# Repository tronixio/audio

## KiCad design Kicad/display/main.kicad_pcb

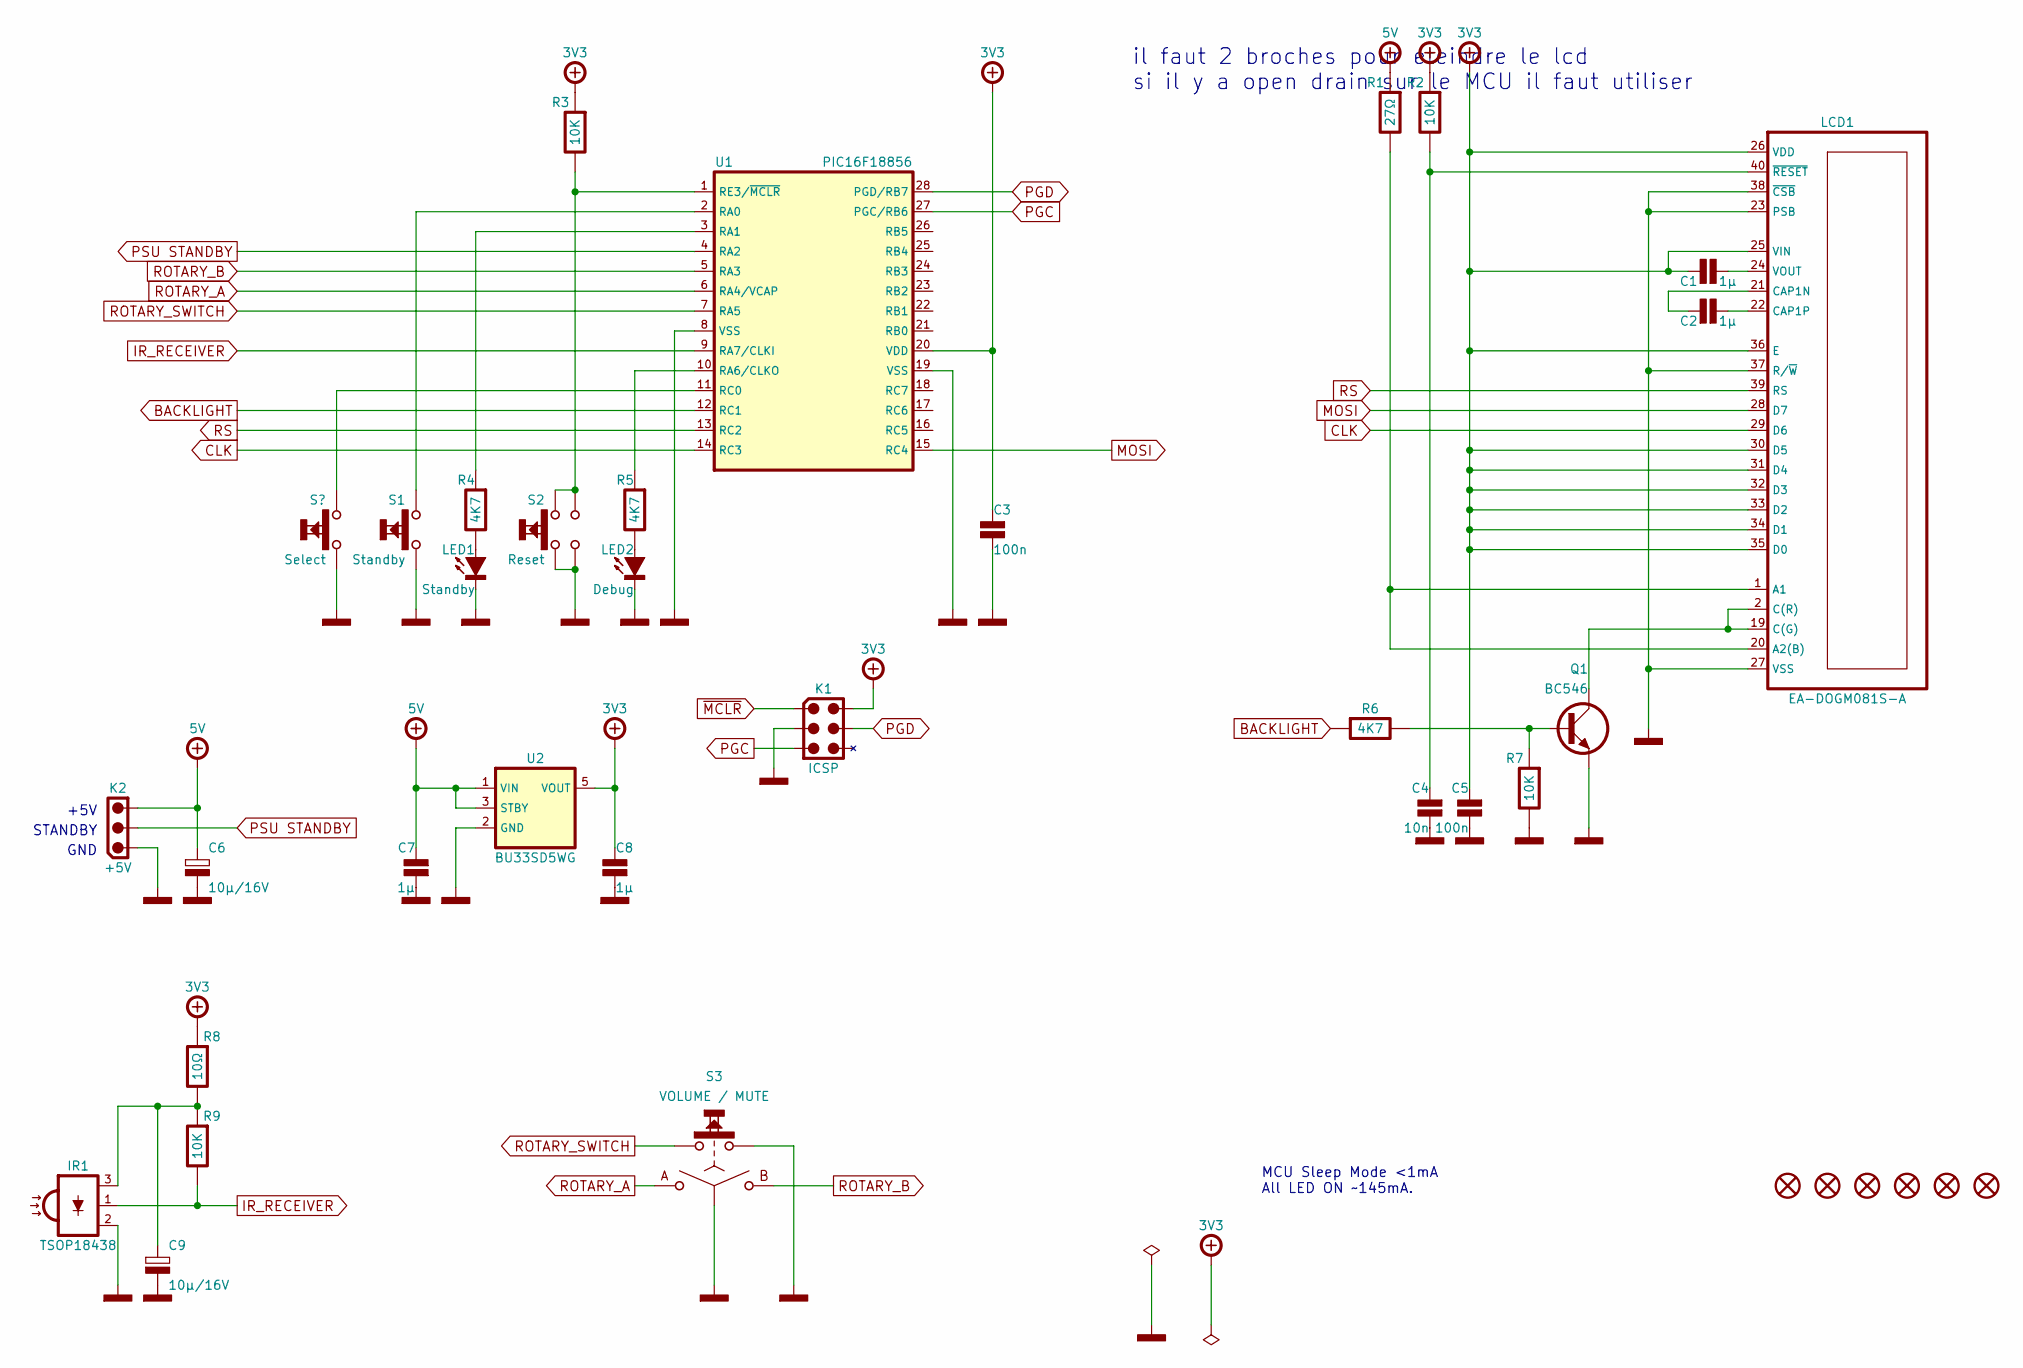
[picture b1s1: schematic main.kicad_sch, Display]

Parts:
C1, C2, C7, C8: 1µ; CAPACITOR-SMD-1206; Voltage 50V; Tolerance 20%; Mouser 80-C1206C105M5R
C3, C5: 100n; CAPACITOR-SMD-1206; Voltage 50V; Tolerance 20%; Mouser 80-C1206C104M5R
C4: 10n; CAPACITOR-SMD-1206; Voltage 50V; Tolerance 20%; Mouser 80-C1206C103M5R
C6, C9: 10µ/16V; CAPACITOR-ELECTROLYTIC-SMD-040-054; Tolerance 20%; Voltage 16V; Mouser 647-UWX1C100MCL1
H1, H2, H3, H4, H5, H6: MOUNTING-HOLE-3MM-MASK
IR1: TSOP18438; VISHAY-MINICAST-HORIZONTAL; Mouser 78-TSOP18438
K1: ICSP; HARWIN-M20-998034x; Mouser 855-M20-9980346
K2: +5V; MOLEX-532580329; Mouser 538-53258-0329
LCD1: EA-DOGM081S-A; EA-DOGMXXX-A; Mouser 790-EADOGM081SA
LED1: Standby; LED-SMD-1206; Mouser 604-APT3216LZGCK
LED2: Debug; LED-SMD-1206; Mouser 604-APT3216LZGCK
Q1: BC546; TO-92-INLINE; Mouser 512-BC546ABU
R1: 27Ω; RESISTOR-SMD-0805; Tolerance 5%; Mouser 660-RK73B2ATTDD270J
R2, R3, R7, R9: 10K; RESISTOR-SMD-1206; Tolerance 5%; Mouser 660-RK73B2BTTDD103J
R4, R5, R6: 4K7; RESISTOR-SMD-1206; Tolerance 5%; Mouser 660-RK73B2BTTDD472J
R8: 10Ω; RESISTOR-SMD-1206; Tolerance 5%; Mouser 660-RK73B2BTTDD100J
S1: Standby; CK-PTS635S-TH; Mouser 611-PTS635SH50LFS
S2: Reset; ALPS-SKRPAC; Mouser 688-SKRPACE010
S3: VOLUME / MUTE; BOURNS-PEC16-SWITCH; Mouser 652-PEC164015F-S0024
U1: PIC16F18856; DIP-28-W762; Mouser 579-PIC16F18856-I/SP
U2: BU33SD5WG; SOT-23-5; Mouser 755-BU33SD5WG-TR

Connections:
+3V3: C1.1, C3.1, C5.1, C8.2, K1.2 (VDD), LCD1.25 (VIN), LCD1.26 (VDD), LCD1.30 (D5), LCD1.31 (D4), LCD1.32 (D3), LCD1.33 (D2), LCD1.34 (D1), LCD1.35 (D0), LCD1.36 (E), R2.2, R3.2, R8.2, U1.20 (VDD), U2.5 (VOUT)
+5V: C6.1, C7.2, K2.3, R1.2, U2.1 (VIN), U2.3 (STBY)
BACKLIGHT: R6.2, U1.12 (RC1)
CLK: LCD1.29 (D6), U1.14 (RC3)
GND: C3.2, C4.2, C5.2, C6.2, C7.1, C8.1, C9.2, IR1.2 (GND), K1.3 (GND), K2.1, LCD1.23 (PSB), LCD1.27 (VSS), LCD1.37 (R/~W), LCD1.38 (~CSB), LED1.1 (C), LED2.1 (C), Q1.3 (E), R7.1, S1.1, S2.1, S2.2, S3.2 (C), S3.4, U1.8 (VSS), U1.19 (VSS), U2.2 (GND)
IR_RECEIVER: IR1.1 (OUT), R9.1, U1.9 (RA7/CLKI)
MOSI: LCD1.28 (D7), U1.15 (RC4)
unnamed: C1.2, LCD1.24 (VOUT)
unnamed: C2.1, LCD1.21 (CAP1N)
unnamed: C2.2, LCD1.22 (CAP1P)
unnamed: C4.1, LCD1.40 (~RESET), R2.1
unnamed: C9.1, IR1.3 (V), R8.1, R9.2
unnamed: LCD1.1 (A1), LCD1.20 (A2(B)), R1.1
unnamed: LCD1.2 (C(R)), LCD1.19 (C(G)), Q1.1 (C)
unnamed: LED1.2 (A), R4.1
unnamed: LED2.2 (A), R5.1
unnamed: Q1.2 (B), R6.1, R7.2
unnamed: R3.1, S2.3, S2.4, U1.1 (RE3/~MCLR)
unnamed: R4.2, U1.3 (RA1)
unnamed: R5.2, U1.10 (RA6/CLKO)
unnamed: S1.2, U1.2 (RA0)
PGC: K1.5 (PGC), U1.27 (PGC/RB6)
PGD: K1.4 (PGD), U1.28 (PGD/RB7)
PSU STANDBY: K2.2, U1.4 (RA2)
ROTARY_A: S3.1 (A), U1.6 (RA4/VCAP)
ROTARY_B: S3.3 (B), U1.5 (RA3)
ROTARY_SWITCH: S3.5, U1.7 (RA5)
RS: LCD1.39 (RS), U1.13 (RC2)
~MCLR: K1.1 (~MCLR)

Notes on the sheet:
+5V
GND
STANDBY
il faut 2 broches pour eteindre le lcd si il y a open drain sur le MCU il faut utiliser
MCU Sleep Mode <1mA All LED ON ~145mA.

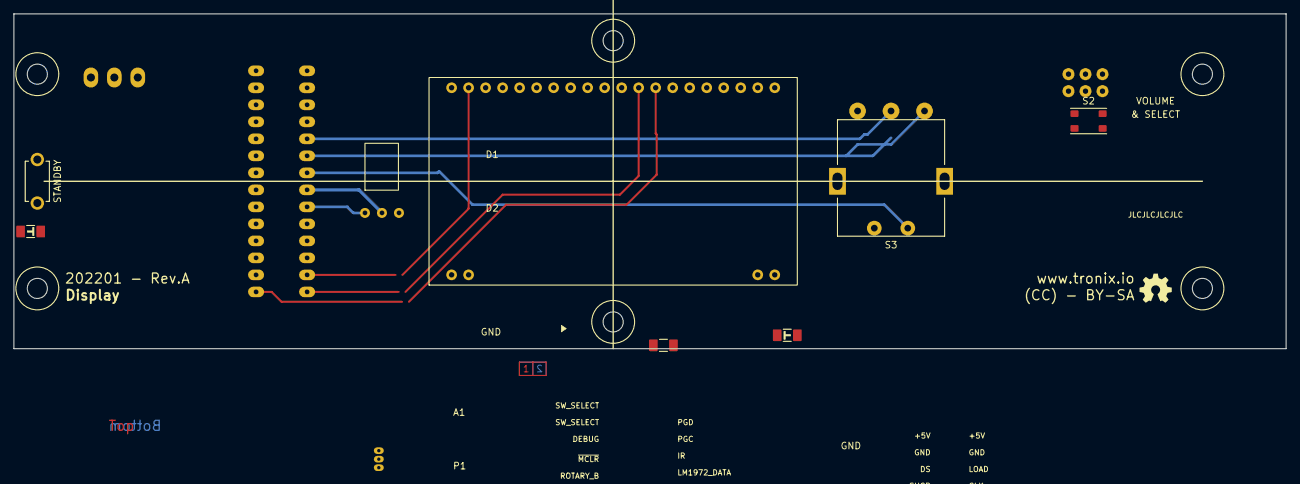
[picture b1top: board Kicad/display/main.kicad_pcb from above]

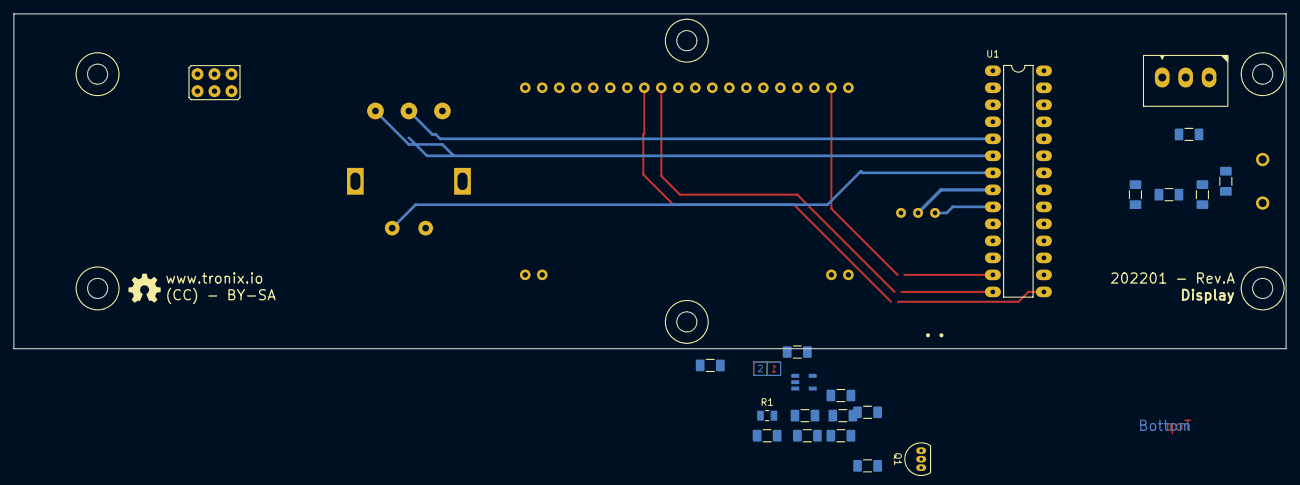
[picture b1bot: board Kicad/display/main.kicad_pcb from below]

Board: 2 copper layers, 190.0 x 50.0 mm, 37 parts (22 on the bottom side), 28 nets.

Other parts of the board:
GB: LOGO; OSHW-5MM
GT: LOGO; OSHW-5MM

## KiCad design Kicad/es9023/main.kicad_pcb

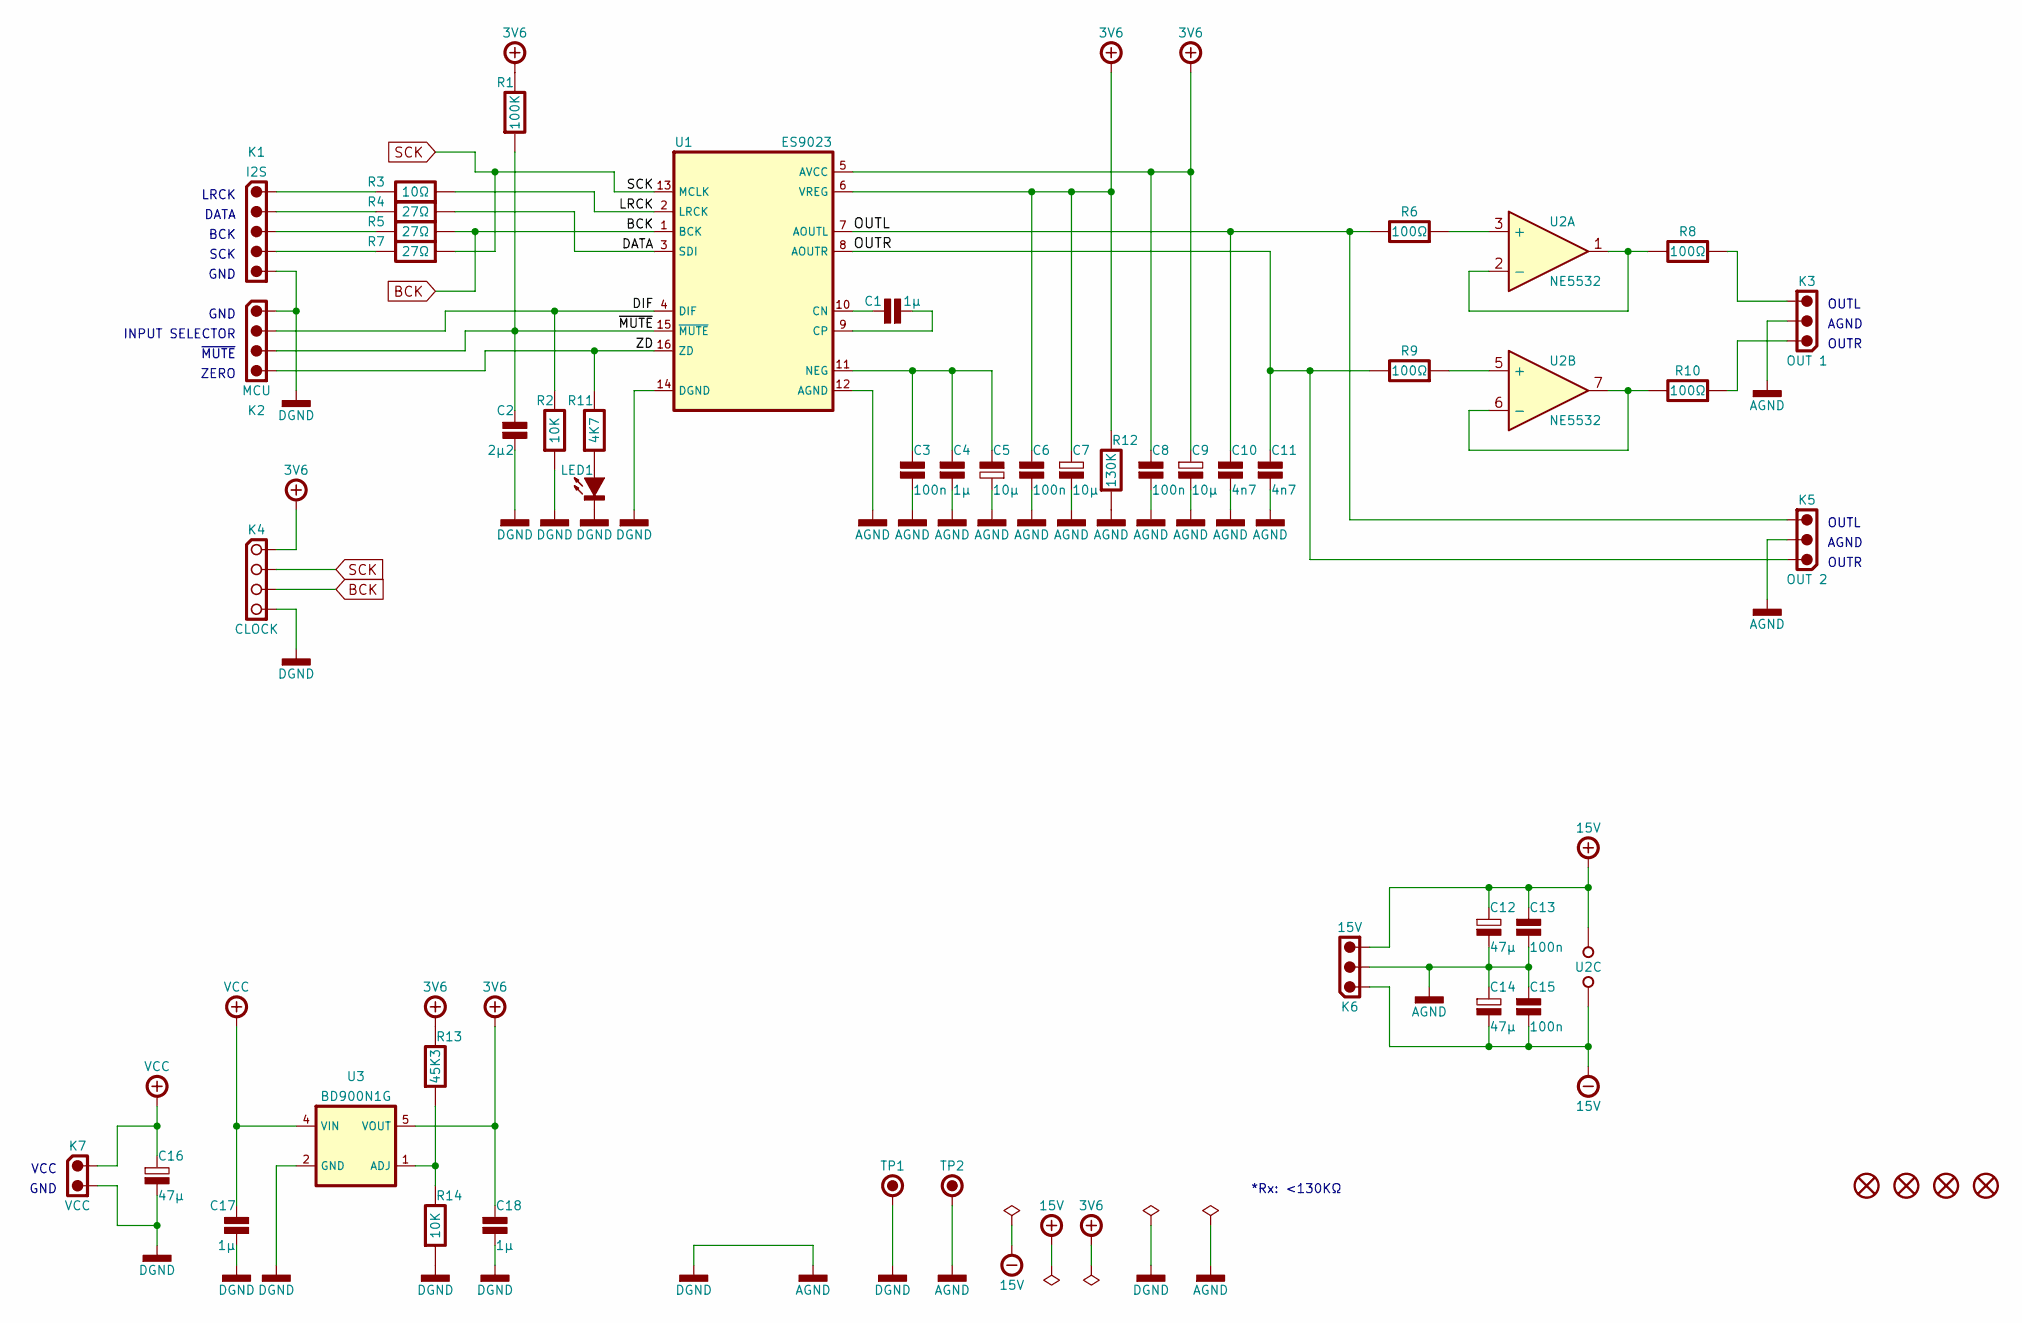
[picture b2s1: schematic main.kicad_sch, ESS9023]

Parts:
C1, C4, C17, C18: 1µ; CAPACITOR-SMD-1206; Voltage 50V; Tolerance 20%; Mouser 80-C1206C105M5R
C2: 2µ2; CAPACITOR-SMD-1206; Voltage 50V; Tolerance 20%; Mouser 80-C1206C105M5R
C3, C6, C8, C13, C15: 100n; CAPACITOR-SMD-1206; Voltage 50V; Tolerance 20%; Mouser 80-C1206C105M5R
C5, C7, C9: 10µ; CAPACITOR-ELECTROLYTIC-RADIAL-050-110-020-WURTH; Voltage 63V; Tolerance 20%; Mouser 710-860010772009
C10, C11: 4n7; CAPACITOR-SMD-1206; Voltage 50V; Tolerance 20%; Mouser 80-C1206C105M5R
C12, C14, C16: 47µ; CAPACITOR-ELECTROLYTIC-RADIAL-050-110-020-WURTH; Tolerance 20%; Voltage 35V; Mouser 710-860010572005
H1, H2, H3, H4: MOUNTING-HOLE-3MM-MASK
K1: I2S; MOLEX-532530570; Mouser 538-53253-0570
K2: MCU; HARWIN-M20-999044x; Mouser 855-M20-999044
K3: OUT 1; MOLEX-532530370; Mouser 538-53253-0370
K4: CLOCK; HARWIN-M20-782044x; Mouser 855-M20-782044
K5: OUT 2; MOLEX-532530370; Mouser 538-53253-0370
K6: 15V; MOLEX-532580329; Mouser 538-53258-0329
K7: VCC; MOLEX-532580229; Mouser 538-53258-0229
LED1: Zero; LED-SMD-1206; Mouser 604-APT3216LSECKJ3RV
R1: 100K; RESISTOR-SMD-1206; Tolerance 5%; Mouser 660-RK73B2BTTDD104J
R2: 10K; RESISTOR-SMD-1206; Tolerance 5%; Mouser 660-RK73B2BTTDD103J
R3: 10Ω; RESISTOR-SMD-1206; Tolerance 1%; Mouser 603-RT1206FRE1310RL
R4, R5, R7: 27Ω; RESISTOR-SMD-1206; Tolerance 1%; Mouser 603-RT1206FRE0727RL
R6, R8, R9, R10: 100Ω; RESISTOR-SMD-1206; Tolerance 5%; Mouser 660-RK73B2BTTDD101J
R11: 4K7; RESISTOR-SMD-1206; Tolerance 5%; Mouser 660-RK73B2BTTDD472J
R12: 130K; RESISTOR-SMD-1206; Tolerance 5%; Mouser 660-RK73B2BTTDD133J
R13: 45K3; RESISTOR-SMD-1206; Tolerance 1%; Mouser 603-RT1206FRE1310KL
R14: 10K; RESISTOR-SMD-1206; Tolerance 1%; Mouser 603-RT1206FRE1310KL
TP1, TP2: GND; KEYSTONE-5006; Mouser 534-5006
U1: ES9023; SOP-16; Mouser 460-ES9023P
U2: NE5532; DIP-08-W762; Mouser 595-NE5532P
U3: BD900N1G; SOT-23-5; Mouser 755-BD900N1G-CTR

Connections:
+3V6: C6.1, C7.1, C8.1, C9.1, C18.1, K4.1, R1.1, R12.1, R13.1, U1.5 (AVCC), U1.6 (VREG), U3.5 (VOUT)
+15V: C12.1, C13.1, K6.3, U2.8 (VDD+)
-15V: C14.2, C15.2, K6.1, U2.4 (VDD-)
/DATA: R4.2, U1.3 (SDI)
/DIF: K2.2, R2.1, U1.4 (DIF)
/LRCK: R3.2, U1.2 (LRCK)
/OUTL: C10.1, K5.3, R6.1, U1.7 (AOUTL)
/OUTR: C11.1, K5.1, R9.1, U1.8 (AOUTR)
/ZD: K2.4, R11.1, U1.16 (ZD)
/~MUTE: C2.1, K2.3, R1.2, U1.15 (~MUTE)
AGND: C2.2, C3.2, C4.2, C5.1, C6.2, C7.2, C8.2, C9.2, C10.2, C11.2, C12.2, C13.2, C14.1, C15.1, C16.2, C17.2, C18.2, K1.5, K2.1, K3.2, K4.4, K5.2, K6.2, K7.2, LED1.1 (C), R2.2, R12.2, R14.2, TP1.1, TP2.1, U1.12 (AGND), U1.14 (DGND), U3.2 (GND)
BCK: K4.3, R5.2, U1.1 (BCK)
unnamed: C1.1, U1.10 (CN)
unnamed: C1.2, U1.9 (CP)
unnamed: C3.1, C4.1, C5.2, U1.11 (NEG)
unnamed: K3.1, R10.2
unnamed: K3.3, R8.2
unnamed: LED1.2 (A), R11.2
unnamed: K1.1, R3.1
unnamed: K1.2, R4.1
unnamed: K1.3, R5.1
unnamed: R6.2, U2.3 (+)
unnamed: K1.4, R7.1
unnamed: R8.1, U2.1, U2.2 (-)
unnamed: R9.2, U2.5 (+)
unnamed: R10.1, U2.6 (-), U2.7
unnamed: R13.2, R14.1, U3.1 (ADJ)
SCK: K4.2, R7.2, U1.13 (MCLK)
VCC: C16.1, C17.1, K7.1, U3.4 (VIN)

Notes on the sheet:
*Rx: <130KΩ
GND
AGND
BCK
SCK
INPUT SELECTOR
OUTL
OUTR
DATA
~{MUTE}
VCC
ZERO
LRCK

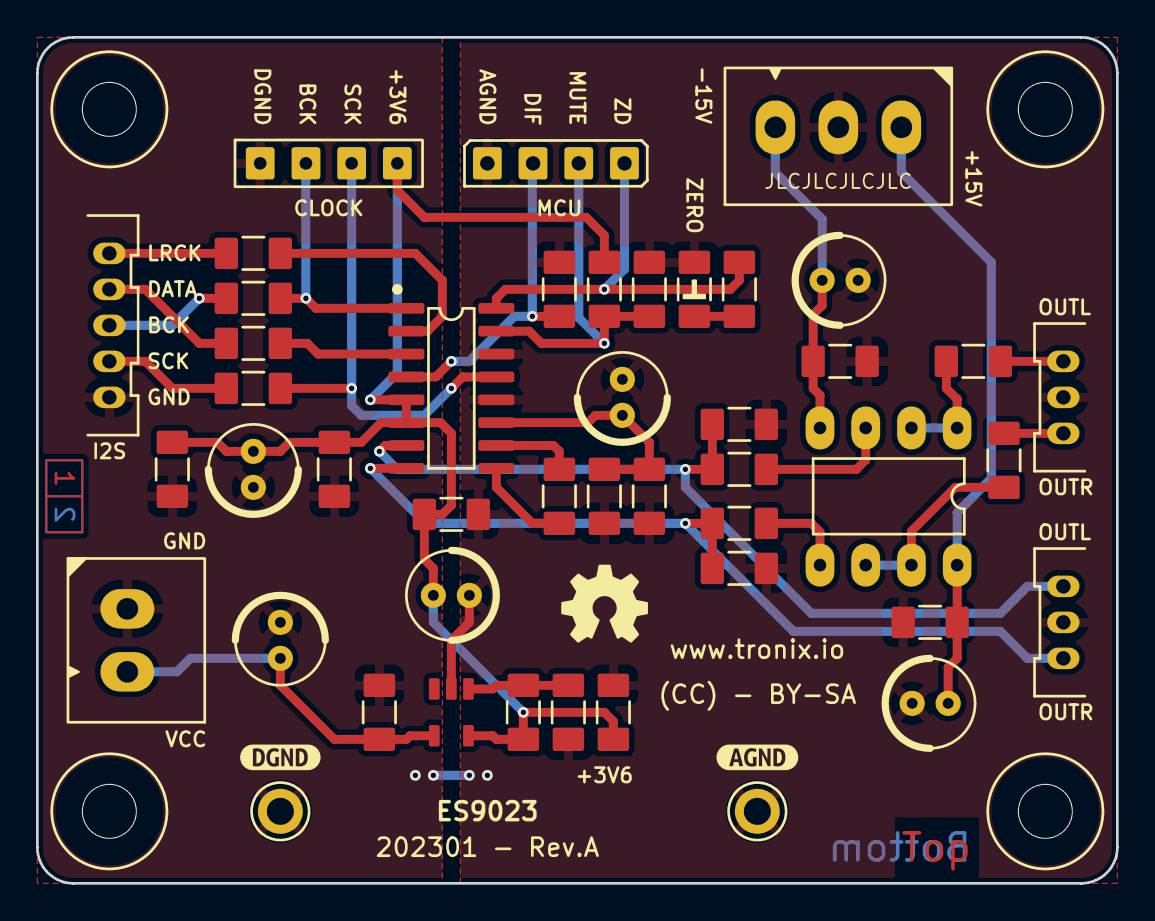
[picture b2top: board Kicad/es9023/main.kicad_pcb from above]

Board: 2 copper layers, 60.0 x 47.0 mm, 51 parts (0 on the bottom side), 29 nets.

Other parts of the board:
kibuzzard-63CAF235: G***; kibuzzard-63CAF235
kibuzzard-63CBA350: G***; kibuzzard-63CBA350

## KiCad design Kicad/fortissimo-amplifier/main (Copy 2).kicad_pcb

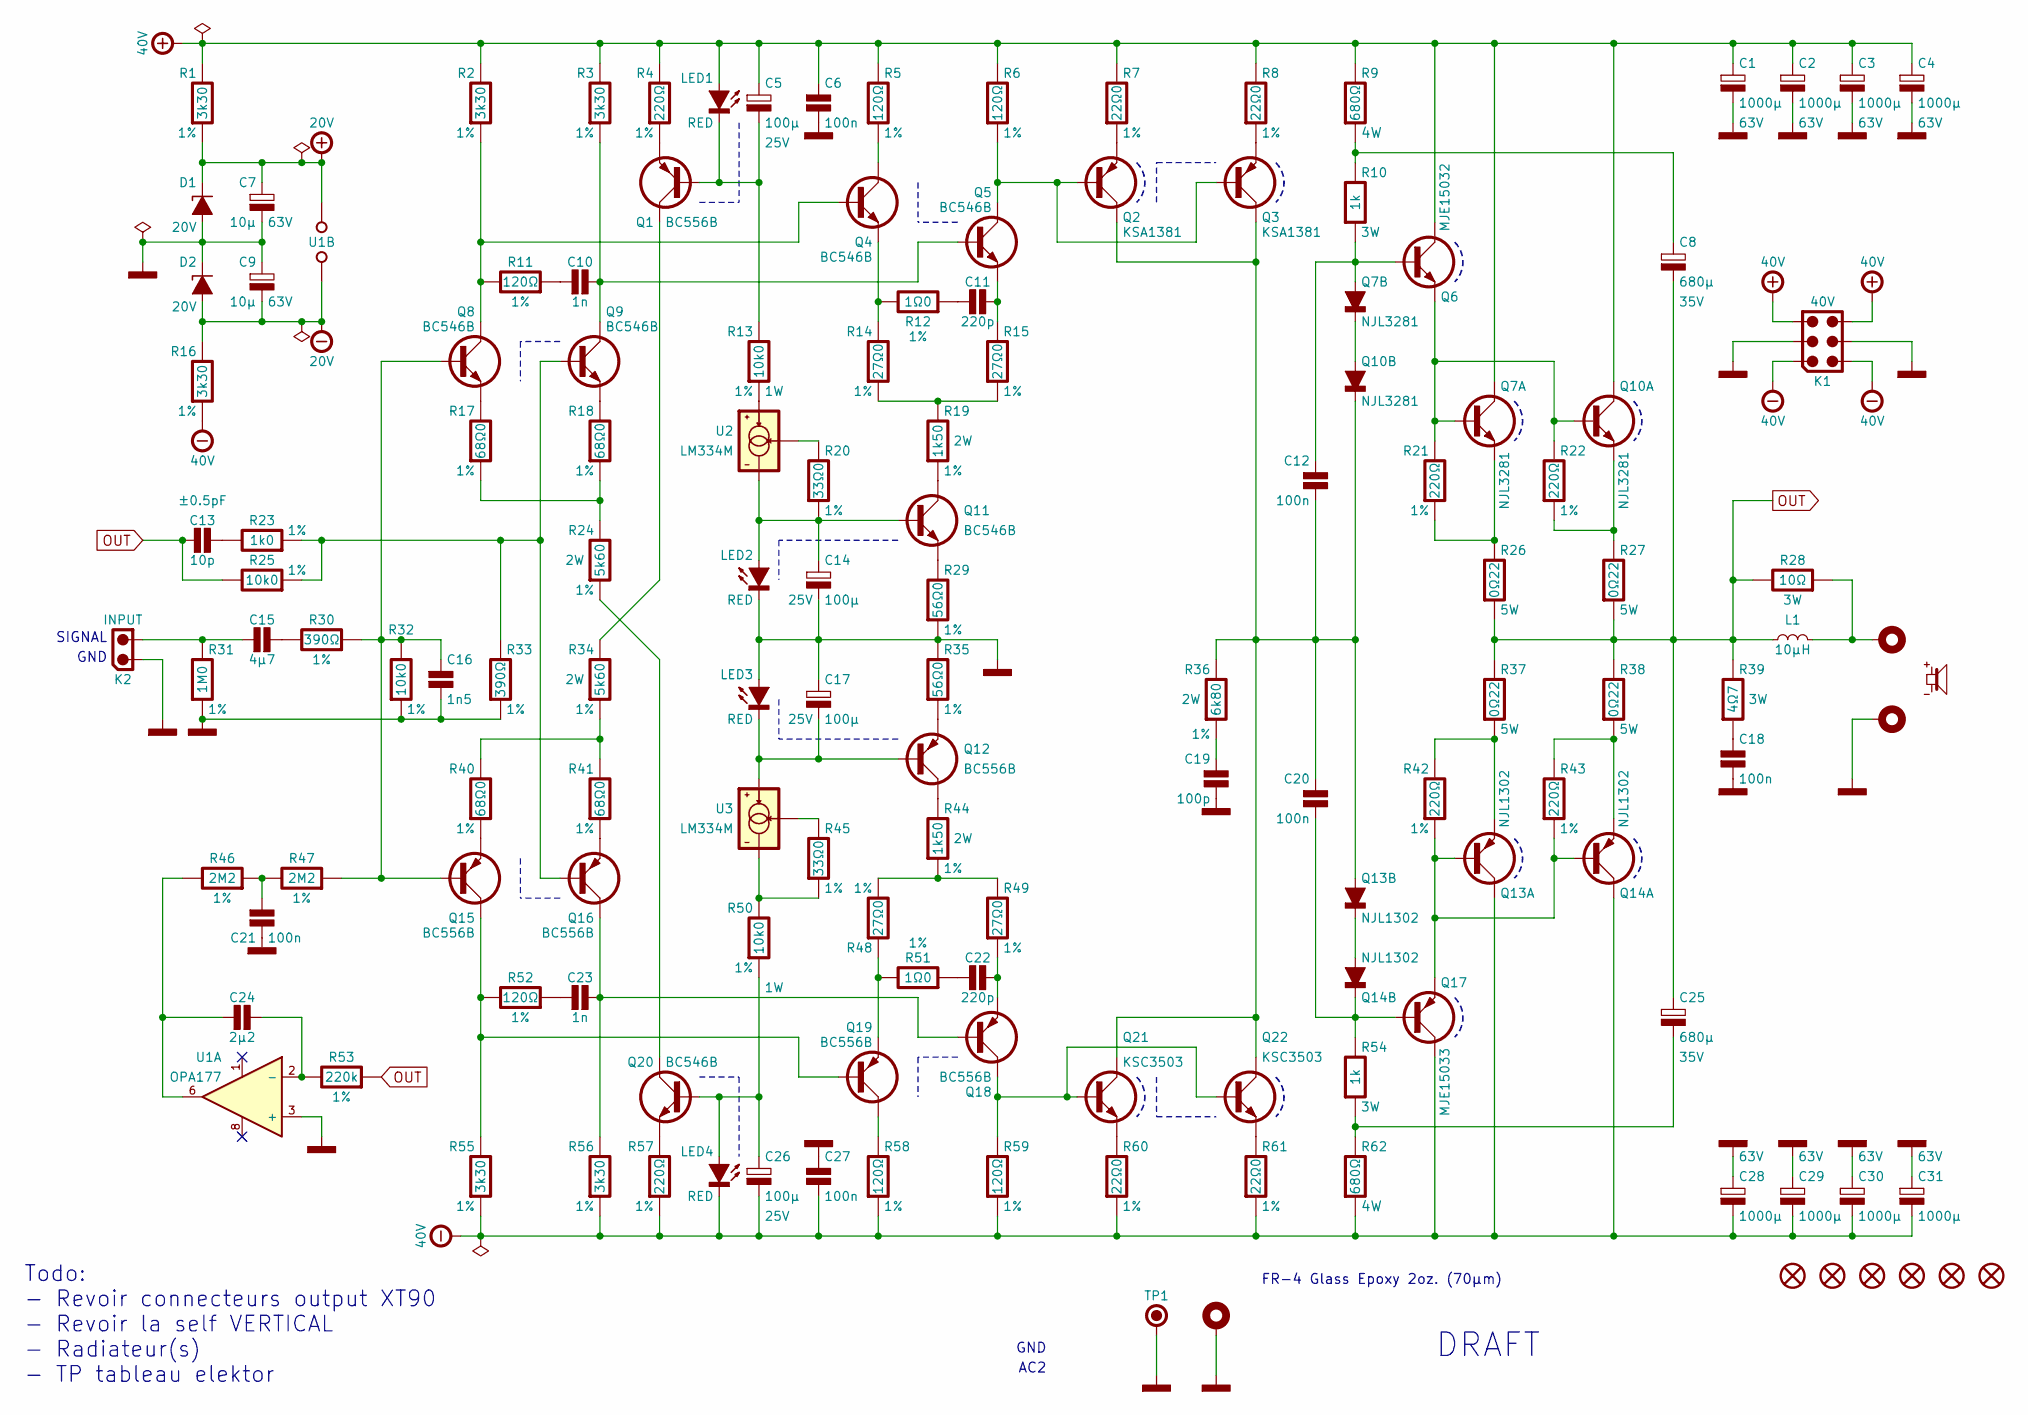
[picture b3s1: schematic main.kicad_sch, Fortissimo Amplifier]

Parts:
C1, C2, C3, C4, C28, C29, C30, C31: 1000µ; CAPACITOR-ELECTROLYTIC-RADIAL-160-350-075-WURTH; Voltage 63V; Tolerance 20%; Mouser 710-860040780017
C5, C14, C17, C26: 100µ; CAPACITOR-ELECTROLYTIC-RADIAL-080-115-035-WURTH; Tolerance 20%; Voltage 25V; Mouser 710-860240474005
C6, C12, C20, C21, C27: 100n; WIMA-FILM-CAPACITOR-RADIAL-100-025-070-075; Tolerance 5%; Voltage 100V; Mouser 505-MKS4D031002AJSSD
C7, C9: 10µ; CAPACITOR-ELECTROLYTIC-RADIAL-050-110-020-WURTH; Voltage 63V; Tolerance 20%; Mouser 710-860020772010
C8, C25: 680µ; CAPACITOR-ELECTROLYTIC-RADIAL-130-200-050-WURTH; Voltage 35V; Tolerance 20%; Mouser 710-860080578019
C10, C23: 1n; WIMA-FILM-CAPACITOR-RADIAL-072-025-065-050; Voltage 63V; Tolerance 5%; Mouser 505-FKS2C01101A0JN0
C11, C22: 220p; WIMA-FILM-CAPACITOR-RADIAL-072-045-060-050; Tolerance 2.5%; Voltage 100V; Mouser 505-FKP2220/100/2.5
C13: 10p; CAPACITOR-SMD-1206; Voltage 100V; Tolerance ±0.5pF; Mouser 581-12061A100DAT2A
C15: 4µ7; WIMA-FILM-CAPACITOR-RADIAL-072-085-140-050; Tolerance 5%; Voltage 63V; Mouser 505-MKS24.7/63/5
C16: 1n5; WIMA-FILM-CAPACITOR-RADIAL-072-025-065-050; Voltage 100V; Tolerance 5%; Mouser 505-FKS2D011501A0JA0
C18: 100n; KEMET-R79-100-050-100-050; Tolerance 5%; Voltage 160V; Mouser 80-R79GC3100Z340J
C19: 100p; WIMA-FILM-CAPACITOR-RADIAL-072-045-060-050; Voltage 100V; Tolerance 2.5%; Mouser 505-FKP2100/100/2.5
C24: 2µ2; WIMA-FILM-CAPACITOR-RADIAL-072-072-130-050; Tolerance 5%; Voltage 63V; Mouser 505-MKS22.2/63/5
D1, D2: 20V; SOD-123; Mouser 771-BZT52-C20
H1, H2, H9: MOUNTING-HOLE-3MM-PAD-VIA
H3, H4, H5, H6, H7, H8: MOUNTING-HOLE-3MM-MASK
K1: 40V; MOLEX-39288060; Mouser 538-39-28-8060
K2: INPUT; MOLEX-532530270; Mouser 538-53253-0270
L1: 10µH; WURTH-744710615
LED1, LED2, LED3, LED4: RED; LED-TH-RECTANGULAR-5MM-2MM; Mouser 630-HLMP-S201
Q1, Q12, Q15, Q16, Q18, Q19: BC556B; TO-92-INLINE-WIDE; Mouser 512-BC556BTF
Q2, Q3: KSA1381; TO-126-3-VERTICAL; Mouser 512-KSA1381ESTU
Q4, Q5, Q8, Q9, Q11, Q20: BC546B; TO-92-INLINE-WIDE; Mouser 512-BC546BTF
Q6: MJE15032; TO-220-3-VERTICAL; Mouser 863-MJE15032G
Q7, Q10: NJL3281; TO-264-5-VERTICAL; Mouser 863-NJL3281DG
Q13, Q14: NJL1302; TO-264-5-VERTICAL; Mouser 863-NJL1302DG
Q17: MJE15033; TO-220-3-VERTICAL; Mouser 863-MJE15033G
Q21, Q22: KSC3503; TO-126-3-VERTICAL; Mouser 512-KSC3503DS
R1, R2, R3, R16, R55, R56: 3k30; RESISTOR-SMD-2512; Tolerance 1%; Mouser 603-RC2512FK-073K3L
R4, R21, R22, R42, R43, R57: 220Ω; RESISTOR-SMD-2512; Tolerance 1%; Mouser 603-RC2512FK-07220RL
R5, R6, R11, R52, R58, R59: 120Ω; RESISTOR-SMD-2512; Tolerance 1%; Mouser 603-RC2512FK-07120RL
R7, R8, R60, R61: 22Ω0; RESISTOR-SMD-2512; Tolerance 1%; Mouser 603-RC2512FK-0722RL
R9, R62: 680Ω; RESISTOR-SMD-2816; Tolerance 5%; Mouser 279-3540680RJT
R10, R54: 1k; RESISTOR-SMD-2512-POWER; Tolerance 5%; Mouser 279-35221K0JT
R12, R51: 1Ω0; RESISTOR-SMD-2512; Tolerance 1%; Mouser 603-RC2512FK-071RL
R13, R25, R32, R50: 10k0; RESISTOR-SMD-2512; Tolerance 1%; Mouser 603-RC2512FK-0710KL
R14, R15, R48, R49: 27Ω0; RESISTOR-SMD-2512; Tolerance 1%; Mouser 603-RC2512FK-0727RL
R17, R18, R40, R41: 68Ω0; RESISTOR-SMD-2512; Tolerance 1%; Mouser 603-RC2512FK-0768RL
R19, R44: 1k50; RESISTOR-SMD-2512-POWER; Tolerance 1%; Mouser 279-CRGP2512F1K5
R20, R45: 33Ω0; RESISTOR-SMD-2512; Tolerance 1%; Mouser 603-RC2512FK-0733RL
R23: 1k0; RESISTOR-SMD-2512; Tolerance 1%; Mouser 603-RC2512FK-071KL
R24, R34: 5k60; RESISTOR-SMD-2512-POWER; Tolerance 1%; Mouser 279-CRGP2512F5K6
R26, R27, R37, R38: 0Ω22; KOA-SPEER-BPR58; Tolerance 5%; Mouser 660-BPR58CR22J
R28: 10Ω; RESISTOR-SMD-2512-POWER; Tolerance 5%; Mouser 279-352210RJT
R29, R35: 56Ω0; RESISTOR-SMD-2512; Tolerance 1%; Mouser 603-RC2512FK-0756RL
R30, R33: 390Ω; RESISTOR-SMD-2512; Tolerance 1%; Mouser 603-RC2512FK-07390RL
R31: 1M0; RESISTOR-SMD-2512; Tolerance 1%; Mouser 603-RC2512FK-071ML
R36: 6k80; RESISTOR-SMD-2512; Tolerance 1%; Mouser 279-CRGP2512F6K8
R39: 4Ω7; RESISTOR-SMD-2512-POWER; Tolerance 5%; Mouser 279-35224R7JT
R46, R47: 2M2; RESISTOR-SMD-2512; Tolerance 1%; Mouser 603-RC2512FK-072M2L
R53: 220k; RESISTOR-SMD-2512; Tolerance 1%; Mouser 603-RC2512FK-07220KL
TP1: KEYSTONE-5006; Mouser 534-5006
U1: OPA177; SOIC-08; Mouser 595-OPA177GS/2K5
U2, U3: LM334M; SOIC-08; Mouser 926-LM334MX/NOPB
X1: (no value)

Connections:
+20V: C7.1, D1.1 (C), R1.2, U1.7 (V+)
+40V: C1.1, C2.1, C3.1, C4.1, C5.1, C6.1, K1.3, K1.6, LED1.2 (A), Q6.2 (C), Q7.3 (C), Q10.3 (C), R1.1, R2.1, R3.1, R4.1, R5.1, R6.1, R7.1, R8.1, R9.1
-20V: C9.2, D2.2 (A), R16.1, U1.4 (V-)
-40V: C26.2, C27.2, C28.2, C29.2, C30.2, C31.2, K1.1, K1.4, LED4.1 (C), Q13.3 (C), Q14.3 (C), Q17.2 (C), R16.2, R55.2, R56.2, R57.2, R58.2, R59.2, R60.2, R61.2, R62.2
GND: C1.2, C2.2, C3.2, C4.2, C6.2, C7.2, C9.1, C14.2, C16.2, C17.1, C18.2, C19.2, C21.2, C27.1, C28.1, C29.1, C30.1, C31.1, D1.2 (A), D2.1 (C), H2.1, H9.1, K1.2, K1.5, K2.1, LED2.1 (C), LED3.2 (A), R29.2, R31.2, R32.2, R33.2, R35.1, TP1.1, U1.3 (+)
unnamed: C8.1, R9.2, R10.1
unnamed: C10.1, R11.2
unnamed: C11.1, R12.2
unnamed: C13.2, R23.1
unnamed: C15.1, K2.2, R31.1
unnamed: C15.2, R30.1
unnamed: C18.1, R39.2
unnamed: C19.1, R36.2
unnamed: C21.1, R46.2, R47.1
unnamed: C22.1, R51.2
unnamed: C23.1, R52.2
unnamed: C24.1, R46.1, U1.6
unnamed: C25.2, R54.2, R62.1
unnamed: H1.1, L1.2, R28.2
unnamed: C5.2, LED1.1 (C), Q1.2 (B), R13.1
unnamed: C14.1, LED2.2 (A), Q11.2 (B), R20.2, U2.2 (V-), U2.3 (V-), U2.6 (V-), U2.7 (V-)
unnamed: C17.2, LED3.1 (C), Q12.2 (B), U3.4 (V+)
unnamed: C26.1, LED4.2 (A), Q20.2 (B), R50.2
unnamed: Q1.1 (C), R34.1
unnamed: Q1.3 (E), R4.2
unnamed: Q2.3 (B), Q3.3 (B), Q5.1 (C), R6.2
unnamed: Q2.1 (E), R7.2
unnamed: Q3.1 (E), R8.2
unnamed: Q4.2 (B), Q8.1 (C), R2.2, R11.1
unnamed: Q4.1 (C), R5.2
unnamed: Q4.3 (E), R12.1, R14.1
unnamed: C10.2, Q5.2 (B), Q9.1 (C), R3.2
unnamed: C11.2, Q5.3 (E), R15.1
unnamed: C12.1, Q6.1 (B), Q7.4 (A), R10.2
unnamed: Q7.2 (E), R21.2, R26.1
unnamed: Q8.3 (E), R17.1
unnamed: Q9.3 (E), R18.1
unnamed: Q6.3 (E), Q7.1 (B), Q10.1 (B), R21.1, R22.1
unnamed: Q10.2 (E), R22.2, R27.1
unnamed: Q7.5 (K), Q10.4 (A)
unnamed: C12.2, C20.1, Q2.2 (C), Q3.2 (C), Q10.5 (K), Q13.4 (A), Q21.2 (C), Q22.2 (C), R36.1
unnamed: Q11.1 (C), R19.2
unnamed: Q11.3 (E), R29.1
unnamed: Q12.1 (C), R44.1
unnamed: Q12.3 (E), R35.2
unnamed: Q13.1 (B), Q14.1 (B), Q17.3 (E), R42.2, R43.2
unnamed: Q13.2 (E), R37.2, R42.1
unnamed: Q13.5 (K), Q14.4 (A)
unnamed: Q14.2 (E), R38.2, R43.1
unnamed: C20.2, Q14.5 (K), Q17.1 (B), R54.1
unnamed: C16.1, Q8.2 (B), Q15.2 (B), R30.2, R32.1, R47.2
unnamed: Q15.1 (C), Q19.2 (B), R52.1, R55.1
unnamed: Q15.3 (E), R40.2
unnamed: Q9.2 (B), Q16.2 (B), R23.2, R25.2, R33.1
unnamed: C23.2, Q16.1 (C), Q18.2 (B), R56.1
unnamed: Q16.3 (E), R41.2
unnamed: Q18.1 (C), Q21.3 (B), Q22.3 (B), R59.1
unnamed: C22.2, Q18.3 (E), R49.2
unnamed: Q19.1 (C), R58.1
unnamed: Q19.3 (E), R48.2, R51.1
unnamed: Q20.1 (C), R24.2
unnamed: Q20.3 (E), R57.1
unnamed: Q21.1 (E), R60.1
unnamed: Q22.1 (E), R61.1
unnamed: R14.2, R15.2, R19.1
unnamed: R17.2, R18.2, R24.1
unnamed: R34.2, R40.1, R41.1
unnamed: R44.2, R48.1, R49.1
unnamed: R45.2, R50.1, U3.2 (V-), U3.3 (V-), U3.6 (V-), U3.7 (V-)
unnamed: C24.2, R53.1, U1.2 (-)
unnamed: R20.1, U2.1 (R)
unnamed: R13.2, U2.4 (V+)
unnamed: R45.1, U3.1 (R)
OUT: C8.2, C13.1, C25.1, L1.1, R25.1, R26.2, R27.2, R28.1, R37.1, R38.1, R39.1, R53.2

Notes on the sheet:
FR-4 Glass Epoxy 2oz. (70µm)
GND
DRAFT
SIGNAL
AC2
Todo: - Revoir connecteurs output XT90 - Revoir la self VERTICAL - Radiateur(s) - TP tableau elektor

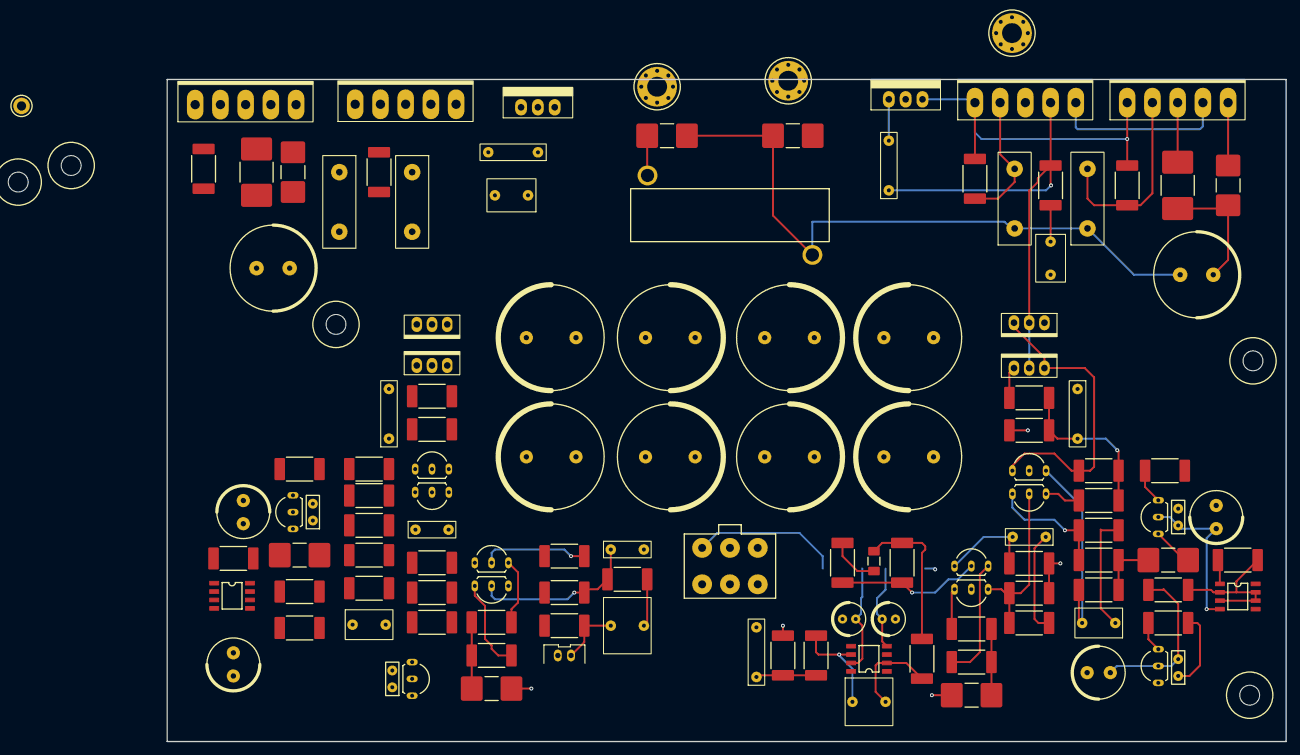
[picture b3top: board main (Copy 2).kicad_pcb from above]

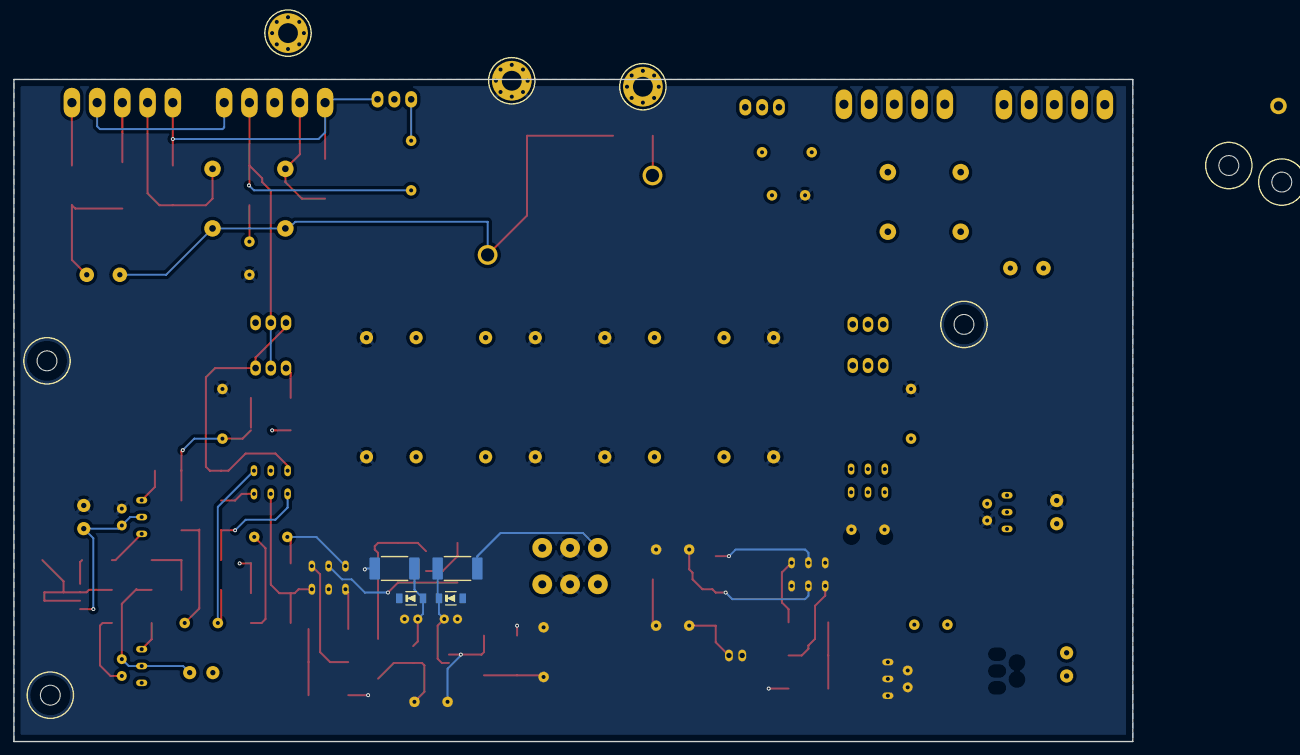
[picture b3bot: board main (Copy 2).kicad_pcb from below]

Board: 4 copper layers, 169.0 x 100.0 mm, 138 parts (4 on the bottom side), 74 nets.

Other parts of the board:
kibuzzard-65E2F8E3: G***; kibuzzard-65E2F8E3
